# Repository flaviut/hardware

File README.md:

# hardware_projects

Run `./scripts/jlcpcb_fab.py <project_dir>` to generate a JLCPCB-ready gerber + drill zip at `<project_dir>/fab/`.

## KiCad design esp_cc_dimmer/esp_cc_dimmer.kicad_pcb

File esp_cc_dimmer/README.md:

# ESP CC Dimmer

A Wi-Fi constant-current LED dimmer running ESPHome.

## Intended use

Designed to clamp onto wire shelving to dim a plant grow-light string. The
3D-printed enclosure bolts to two **shelf nuts** that slot behind the wire grid;
two M3×20 bolts and nylock nuts pinch the shelf wire between box and nuts. The
knob allows offline dimming.

## Power supply

Requirements:

- **10–56 V DC**, set by the NLDD-H input range (the board silk marks the 48 V
  design point).
- At least ~2 V above the LED string's forward voltage. Read your LED strip's datasheet.
- Current capacity ≥ your LED string + 50mA for the electronics.

## How it works

- **Power in (J2):** 10–56 V feeds both the NLDD driver and an LX8015 buck that
  derives 3V3 for the MCU.
- **Dimming:** the ESP32-C3 drives the NLDD's PWM dim input at 50 kHz (LEDC) —
  high-frequency PWM keeps the driver silent.
- **LED out (J1):** constant-current string from the NLDD-H.
- **Controls:** EC11 rotary encoder (turn = ±5 % brightness, press = toggle).
- **Sensing:** VEML7700 ambient-light sensor on I²C (GPIO6/7).

## Renders

| PCB top | PCB bottom |
|---------|------------|
|  |  |

| Enclosure base | Lid |
|----------------|-----|
|  |  |

| Knob | Shelf nut (×2) |
|------|----------------|
|  |  |

## Bill of Materials

Board: **68.25 × 52.0 mm**, 2-layer.

### Electronics

| Refs | Qty | Value / Part | Package | Notes |
|------|-----|--------------|---------|-------|
| U3 | 1 | Seeed XIAO ESP32-C3 | | |
| PS1 | 1 | Mean Well NLDD-1050H | | Any NLDD-350/500/700/1050H fits |
| U4 | 1 | LX8015 | | 3V3 for the MCU |
| U2 | 1 | Vishay VEML7700 | 6-pin OPLGA | I²C ambient-light sensor |
| SW1 | 1 | Alps EC11E15244G1 | EC11 vertical | Rotary encoder with push switch |
| J1, J2 | 2 | WJ15EDGRC-3.81-02P (clone) / Phoenix Contact MCV 1,5/2-G-3,81 — 1803426 (original) | | Board-side pluggable headers (power in / LED out) |
| (mates J1, J2) | 2 | WJ15EDGK-3.81-02P-14-00A (clone) / Phoenix Contact MC 1,5/2-ST-3,81 — 1803578 (original) | | Wire-side screw plug for each header |
| C2 | 1 | 100 µF 63 V | Radial Ø8 mm | |
| C11 | 1 | 4.7 µF 100 V | 1210 | |
| C8 | 1 | 10 µF | 1210 | |
| C1, C3 | 2 | 1 µF | 0603 | |
| R1, R2 | 2 | 4.7 kΩ | 0603 | |

### Mechanical

| Qty | Part | Notes |
|-----|------|-------|
| 1 | Enclosure base + lid | Print `enclosure/esp_cc_dimmer_box.stl` (both parts) |
| 1 | Dimmer knob | Print `enclosure/dimmer_knob_textured.stl` |
| 2 | Shelf nut | Print `enclosure/shelf_nut.step` |
| 2 | M3 × 20 mm bolt | Clamps box to shelf nuts |
| 2 | M3 nylock nut | — |

## Printing

- **Knob** (`dimmer_knob_textured.stl`): 0.12 mm layers, ironed top surface. The
  leaf texture was applied to the base model with [bumpmesh.com](https://bumpmesh.com)
  (`dimmer_knob.bumpmesh` + `leaves.png`).
- **Enclosure / shelf nuts:** standard 0.2 mm, no supports.

## Firmware

ESPHome config: [`esphome/esp-cc-dimmer.yaml`](esphome/esp-cc-dimmer.yaml).
Provide `wifi_ssid` / `wifi_password` via `secrets.yaml`, then:

```sh
esphome run esphome/esp-cc-dimmer.yaml
```

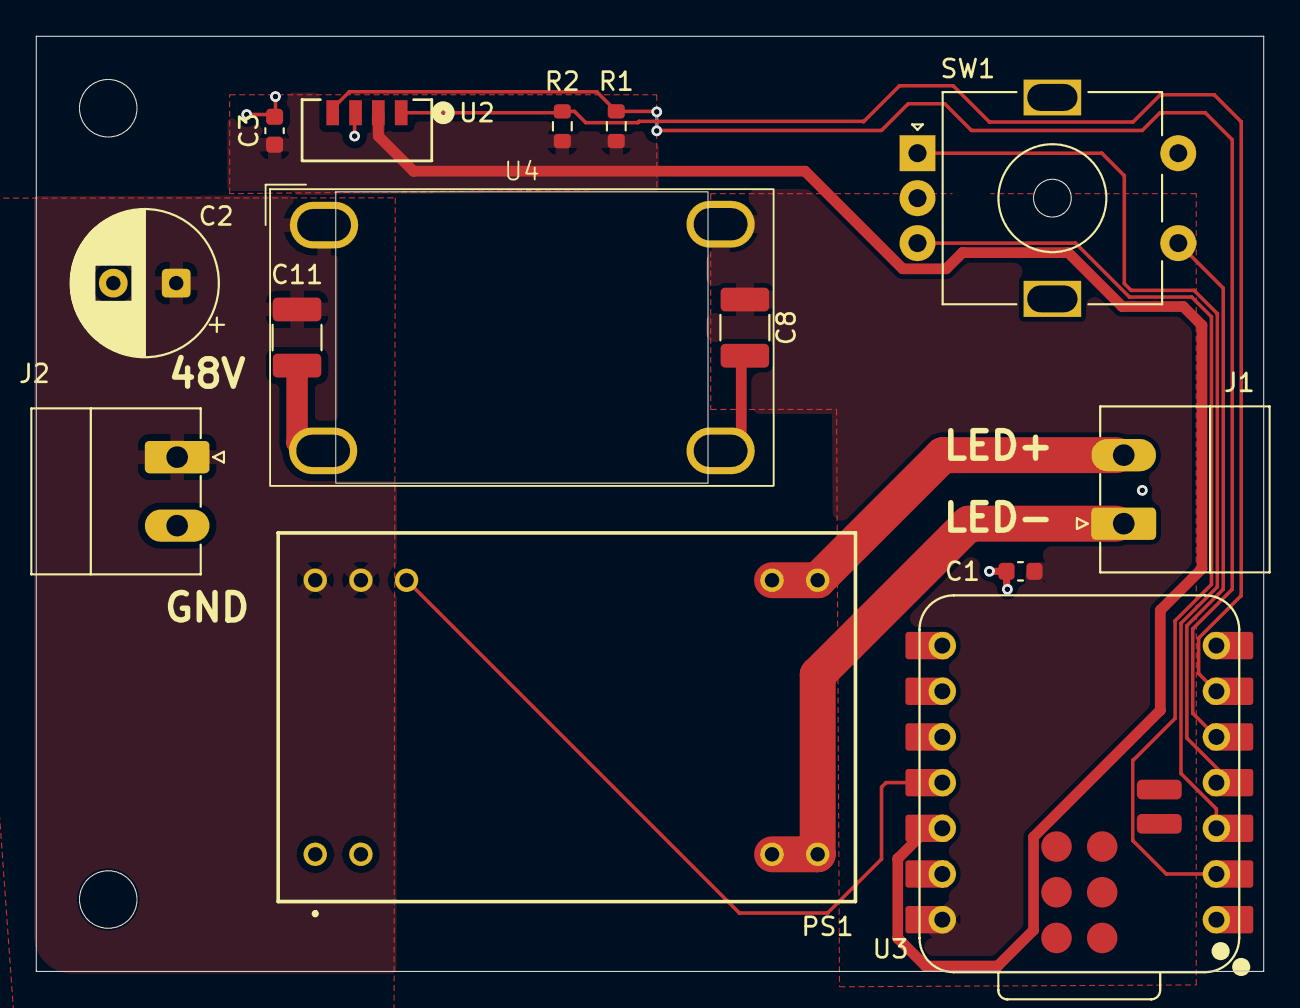
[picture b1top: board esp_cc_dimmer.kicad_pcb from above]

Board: 2 copper layers, 68.2 x 52.0 mm, 16 parts (0 on the bottom side), 12 nets.

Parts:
C1, C3: 1uF; C_0603_1608Metric
C2: 100u 63V; CP_Radial_D8.0mm_P3.50mm
C8: 10u; C_1210_3225Metric_Pad1.33x2.70mm_HandSolder
C11: 4.7u 100V; C_1210_3225Metric_Pad1.33x2.70mm_HandSolder
H1, H2: MountingHole; MountingHole_3.2mm_M3
J1, J2: WJ15EDGRC-3.81-02P-14-00A; PhoenixContact_MC_1,5_2-G-3.81_1x02_P3.81mm_Horizontal
PS1: NLDD-1050H; NLDD1050H
R1, R2: 4.7k; R_0603_1608Metric
SW1: EC11E15244G1; RotaryEncoder_Alps_EC11E-Switch_Vertical_H20mm_MountingHoles
U2: VEML7700-TR
U3: XIAO-ESP32-C3-SMD; XIAO-ESP32-C3-DIP-SMD
U4: LX8015

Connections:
+3V3: C3.1, R1.1, R2.1, U2.2 (VDD), U3.12 (3V3)
+5V: C1.1, C8.1, U3.14 (VBUS), U4.4 (Vout)
+48V: C2.1, C11.1, J2.1, PS1.23 (+VIN_1), PS1.24 (+VIN_2), U4.1 (Vin)
/LED_PWM: PS1.22 (PWM_DIM), U3.11 (GPIO10_D10_MOSI)
/SCL: R2.2, U2.1 (SCL), U3.6 (GPIO7_D5_SCL)
/SDA: R1.2, U2.4 (SDA), U3.5 (GPIO6_D4_SDA)
/Vled+: J1.2, PS1.13 (+VOUT_1), PS1.14 (+VOUT_2)
/Vled-: J1.1, PS1.11 (-VOUT_1), PS1.12 (-VOUT_2)
GND: C1.2, C2.2, C3.2, C8.2, C11.2, J2.2, PS1.1 (-VIN_1), PS1.2 (-VIN_2), SW1.C, SW1.MP, SW1.S2, U2.3 (GND), U3.13 (GND), U4.2 (GND), U4.3 (GND)
unnamed: SW1.B, U3.2 (GPIO3_A1_D1)
unnamed: SW1.A, U3.3 (GPIO4_A2_D2)
unnamed: SW1.S1, U3.4 (GPIO5_A3_D3)

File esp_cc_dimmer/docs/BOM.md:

# Bill of Materials

Board: **68.25 × 52.0 mm**, 2-layer. Reference designators match `esp_cc_dimmer.kicad_sch`.

| # | Refs | Qty | Value / Part | Package | Notes |
|---|------|-----|--------------|---------|-------|
| 1 | U3 | 1 | Seeed XIAO ESP32-C3 | XIAO SMD module | Wi-Fi MCU running ESPHome |
| 2 | PS1 | 1 | Mean Well NLDD-1050H | PCB-mount module | Constant-current LED driver, 10–56 V in, PWM dim. Any NLDD-350/500/700/1050H fits |
| 3 | U4 | 1 | LX8015 | SOT-style buck | Wide-input buck → 3V3 for the MCU |
| 4 | U2 | 1 | Vishay VEML7700 | 6-pin OPLGA | I²C ambient-light sensor |
| 5 | SW1 | 1 | Alps EC11E15244G1 | EC11 vertical | Rotary encoder with push switch (knob) |
| 6 | J1, J2 | 2 | WJ15EDGRC-3.81-02P | 3.81 mm 2-pin | Pluggable terminal blocks (power in / LED out) |
| 7 | C2 | 1 | 100 µF 63 V | Radial Ø8 mm | Input bulk electrolytic |
| 8 | C11 | 1 | 4.7 µF 100 V | 1210 | Buck input cap |
| 9 | C8 | 1 | 10 µF | 1210 | Buck output / 3V3 cap |
| 10 | C1, C3 | 2 | 1 µF | 0603 | Decoupling |
| 11 | R1, R2 | 2 | 4.7 kΩ | 0603 | I²C pull-ups |

**Mechanical (3D-printed):** YAPP_Box enclosure (`enclosure/esp_cc_dimmer_box.3mf`) and encoder knob (`enclosure/dimmer_knob.FCStd`).

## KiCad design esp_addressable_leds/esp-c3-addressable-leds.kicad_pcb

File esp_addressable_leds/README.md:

Waveshare ESP32-C3-Zero based addressable LED driver

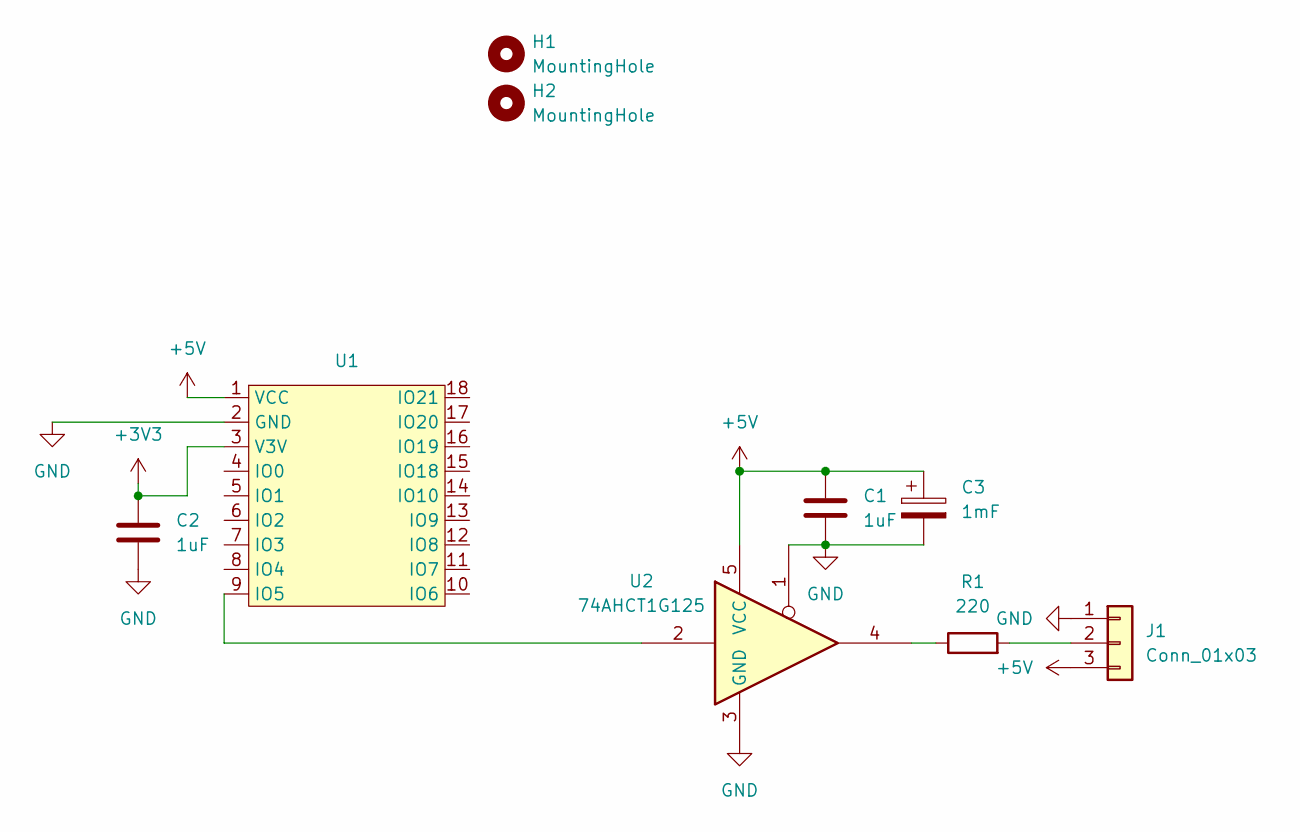
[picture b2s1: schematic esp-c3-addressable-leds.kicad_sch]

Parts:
C1, C2: 1uF; C_0603_1608Metric
C3: 1mF; CP_Radial_D8.0mm_P2.50mm
H1, H2: MountingHole; MountingHole_3.2mm_M3
J1: Conn_01x03; SolderWire-0.5sqmm_1x03_P4.8mm_D0.9mm_OD2.3mm_Relief
R1: 220; R_0603_1608Metric
U1: Waveshare-ESP32-C3-Zero
U2: 74AHCT1G125; SOT-23-5_HandSoldering

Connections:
+3V3: C2.1, U1.3 (V3V)
+5V: C1.1, C3.1, J1.3, U1.1 (VCC), U2.5 (VCC)
GND: C1.2, C2.2, C3.2, J1.1, U1.2 (GND), U2.1, U2.3 (GND)
unnamed: J1.2, R1.2
unnamed: R1.1, U2.4
unnamed: U1.9 (IO5), U2.2

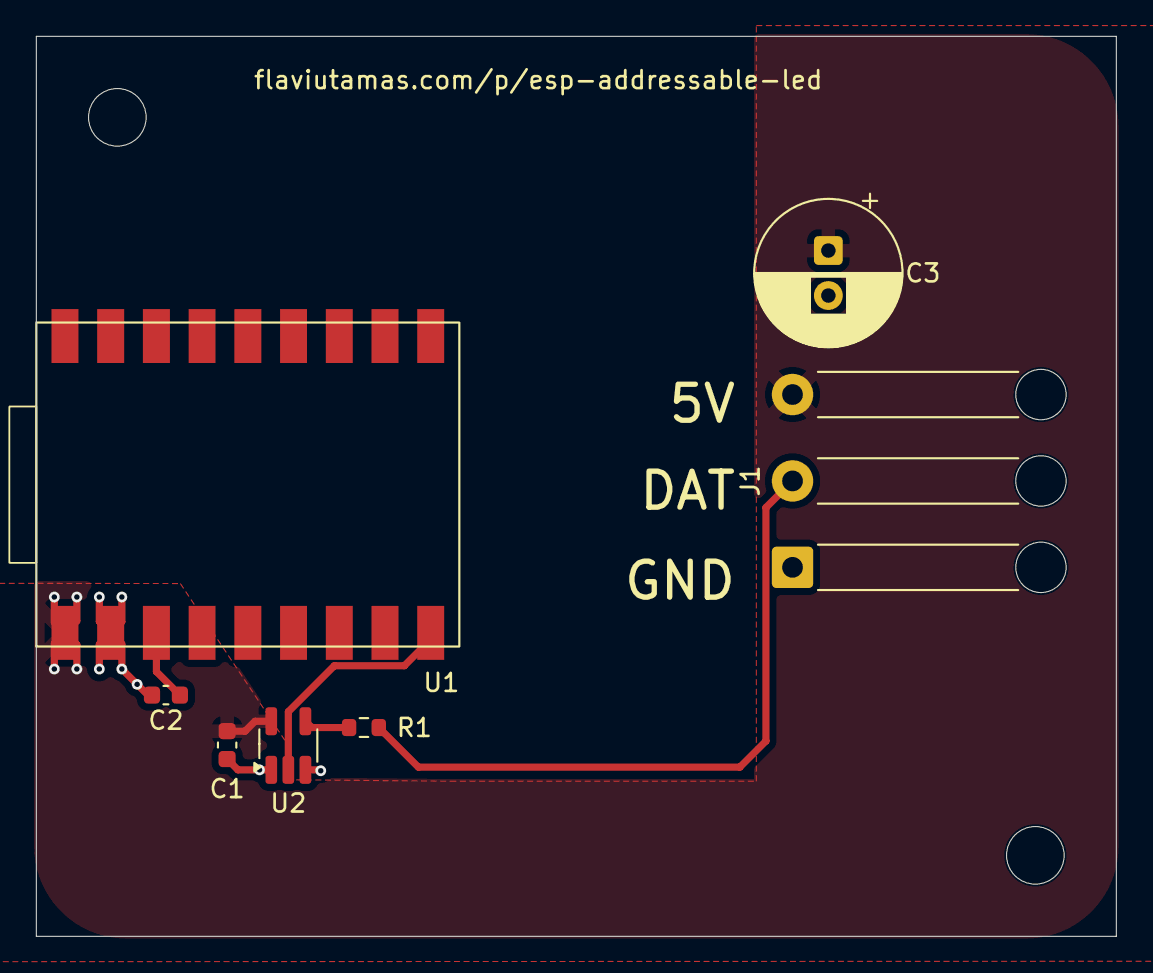
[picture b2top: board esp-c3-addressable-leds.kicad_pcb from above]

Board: 2 copper layers, 60.0 x 50.0 mm, 9 parts (0 on the bottom side), 6 nets.

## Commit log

2026-05-03 second
2026-05-03 update paths
2026-05-04 update:wq
2026-05-04 wip: cc driver
    need to double check esp32 pinout
2026-05-08 done maybe
2026-05-09 add build script
2026-06-27 fix bugs, add esphome config
2026-06-28 add enclosure
2026-06-28 update gitignore
2026-06-28 docs
